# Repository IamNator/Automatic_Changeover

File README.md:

# Automatic Changeover
This project sets out to design a highly effective and efficient IOT enabled automatic changeover for small homes.    
With improvements and modifications as time goes by, this project will design devices capable of allowing the user to monitor their household energy comsumption.

## Files
**3d-module**: contains files of 3D design, (Fusion 360).   
**PCB**: PCB files, (EAGLE).   
**code-mcu**: C program files, (ATMEL Studio).   
**images**: Images of circuit, PCB and 3D designs.   

## How to access this project

 1. Navigate to the main page of this repository.
 2. Under the repository name (Automatic_Changeover), click Clone or download.
 3. In the Clone with HTTPs section, click on **Download Zip** to download this project as a zip file

## Sample Images

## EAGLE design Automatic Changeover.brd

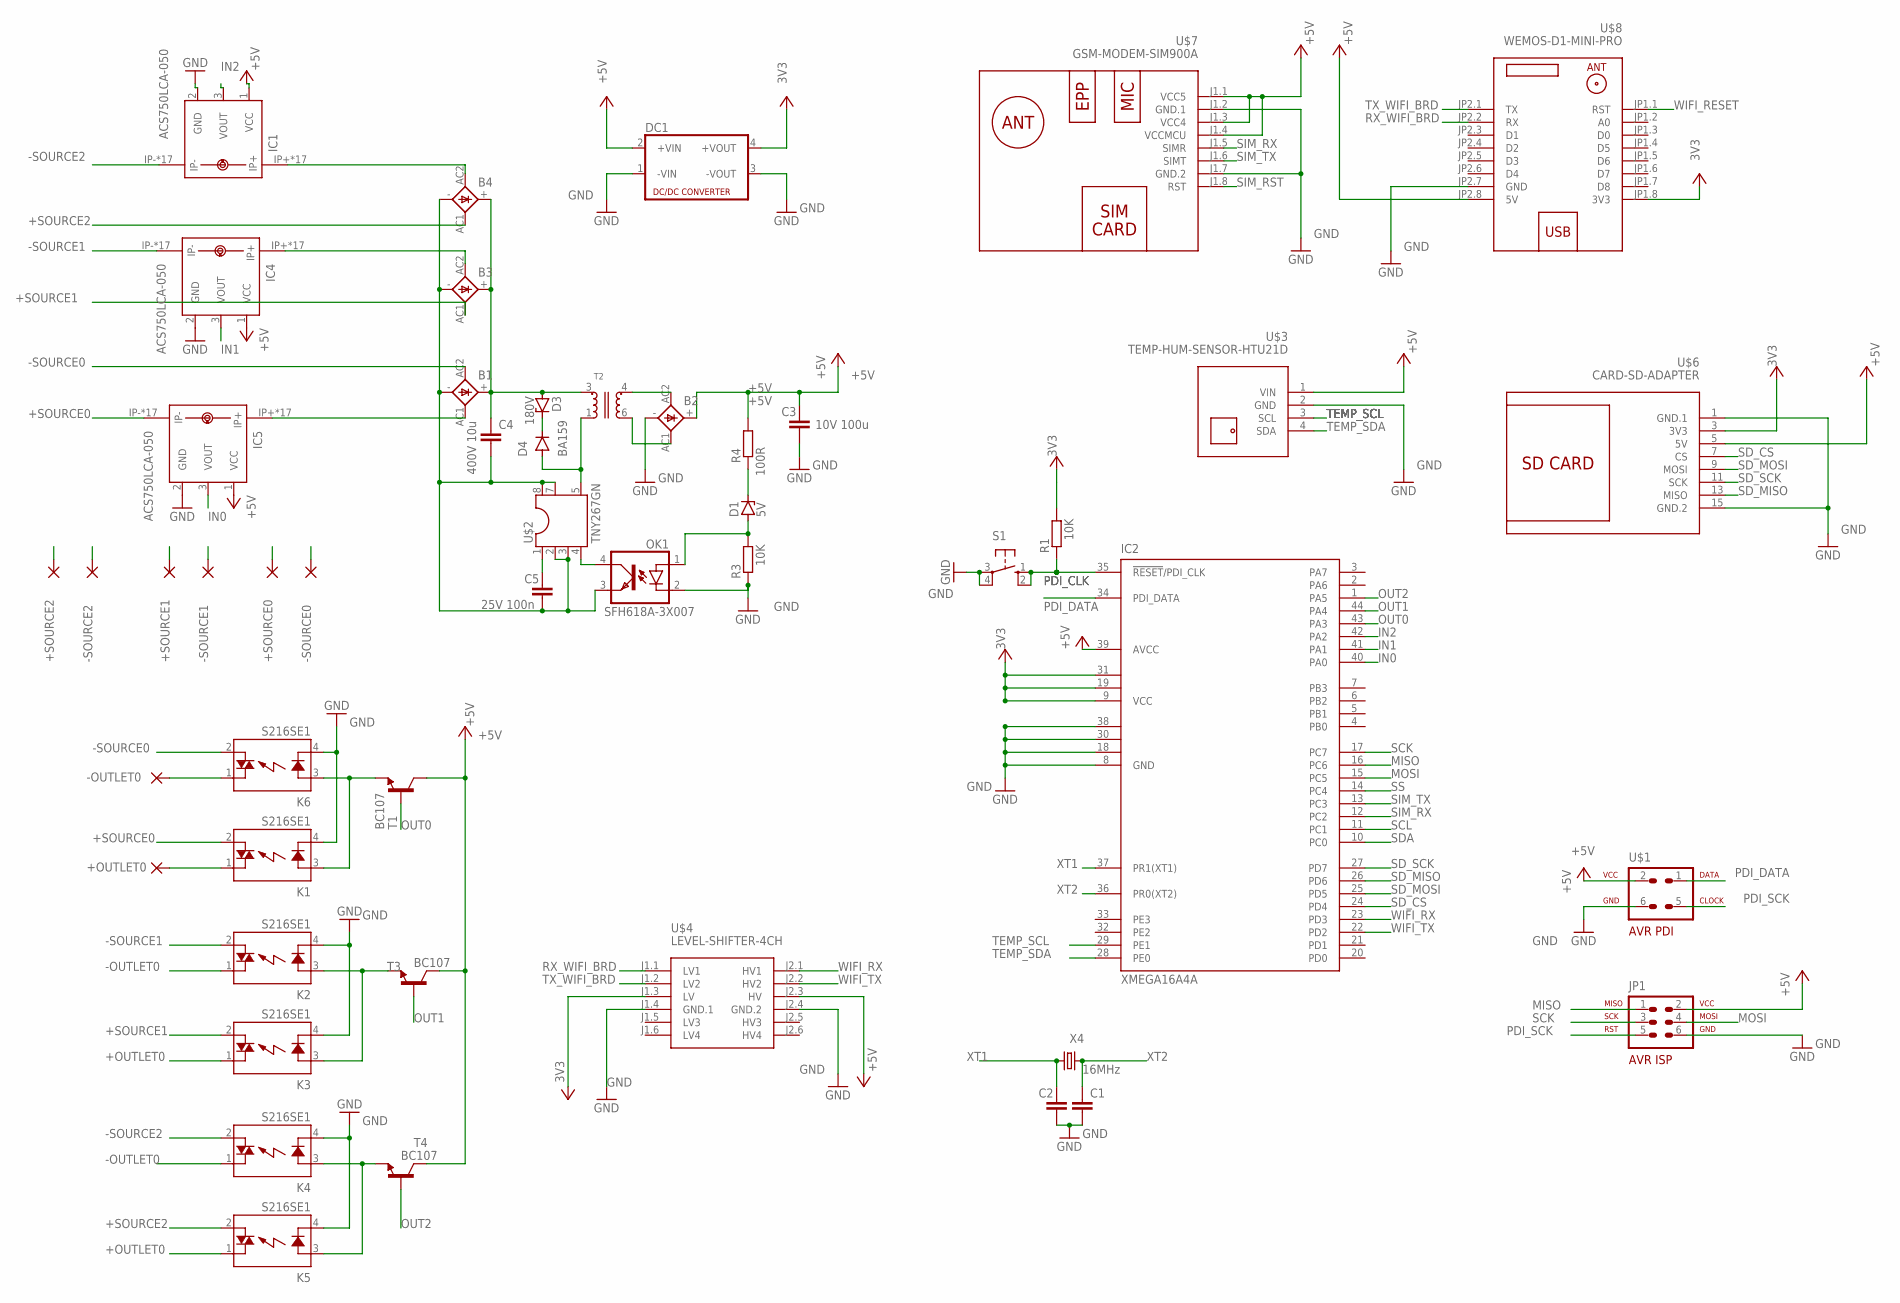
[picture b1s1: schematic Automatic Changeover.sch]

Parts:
+OUTLET0: 3,81/1,4
+SOURCE0, +SOURCE1, +SOURCE2: 3,81/1,4
-OUTLET0: 3,81/1,4
-SOURCE0, -SOURCE1, -SOURCE2: 3,81/1,4
B1, B2, B3, B4: KBL
C1, C2: C-EU025-025X050; C025-025X050
C3: 10V 100u; C2.5-2
C4: 400V 10u; C2.5-2
C5: 25V 100n; C2.5-2
D1: 5V; P1Z12
D3: 180V; P1Z12
D4: BA159; DO41-10
DC1: NME
IC1, IC4, IC5: ACS750LCA-050; ACS75050
IC2: XMEGA16A4A; TQFP44
JP1: AVR-ISP-6VERT; AVR-ISP-6
K1, K2, K3, K4, K5, K6: S216SE1; S2XXEX
OK1: SFH618A-3X007; SMD4-7
R1, R3: 10K; R0805
R4: 100R; R0805
S1: 10-XX; B3F-10XX
T1, T3, T4: BC107; TO18
T2: WE-UNIT_74911810X; WE_E13/7/4_THT_VERTIKAL_6PIN
U$1: AVR-PDIVERT; AVR-ISP-6
U$2: TNY267GN; SMD-8B
U$3: TEMP-HUM-SENSOR-HTU21D
U$4: LEVEL-SHIFTER-4CH
U$6: CARD-SD-ADAPTER
U$7: GSM-MODEM-SIM900A
U$8: WEMOS-D1-MINI-PRO
X4: 16MHz; HC49

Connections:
3V3: DC1.4 (+VOUT), R1.2, U$6.3 (3V3), U$8.JP1.8 (3V3)
+5V: B2.+, C3.1, DC1.2 (+VIN), IC1.1 (VCC), IC2.39 (AVCC), IC4.1 (VCC), IC5.1 (VCC), JP1.2, R4.2, T1.3 (C), T3.3 (C), T4.3 (C), U$1.2, U$3.1 (VIN), U$4.J2.3 (HV), U$6.5 (5V), U$7.J1.1 (VCC5), U$7.J1.3 (VCC4), U$7.J1.4 (VCCMCU), U$8.JP2.8 (5V)
+OUTLET0: K3.1 (DS1), K5.1 (DS1)
+SOURCE0: +SOURCE0.1, IC5.IP-, IC5.IP-@2 (IP-), IC5.IP-@3 (IP-), IC5.IP-@4 (IP-), IC5.IP-@5 (IP-), IC5.IP-@6 (IP-), IC5.IP-@7 (IP-), IC5.IP-@8 (IP-), IC5.IP-@9 (IP-), IC5.IP-@10 (IP-), IC5.IP-@11 (IP-), IC5.IP-@12 (IP-), IC5.IP-@13 (IP-), IC5.IP-@14 (IP-), IC5.IP-@15 (IP-), IC5.IP-@16 (IP-), IC5.IP-@17 (IP-), K1.2 (DS2)
+SOURCE1: +SOURCE1.1, B3.AC1 (AC2), K3.2 (DS2)
+SOURCE2: +SOURCE2.1, B4.AC1 (AC2), K5.2 (DS2)
-OUTLET0: K2.1 (DS1), K4.1 (DS1)
-SOURCE0: -SOURCE0.1, B1.AC2 (AC1), K6.2 (DS2)
-SOURCE1: -SOURCE1.1, IC4.IP-, IC4.IP-@2 (IP-), IC4.IP-@3 (IP-), IC4.IP-@4 (IP-), IC4.IP-@5 (IP-), IC4.IP-@6 (IP-), IC4.IP-@7 (IP-), IC4.IP-@8 (IP-), IC4.IP-@9 (IP-), IC4.IP-@10 (IP-), IC4.IP-@11 (IP-), IC4.IP-@12 (IP-), IC4.IP-@13 (IP-), IC4.IP-@14 (IP-), IC4.IP-@15 (IP-), IC4.IP-@16 (IP-), IC4.IP-@17 (IP-), K2.2 (DS2)
-SOURCE2: -SOURCE2.1, IC1.IP-, IC1.IP-@2 (IP-), IC1.IP-@3 (IP-), IC1.IP-@4 (IP-), IC1.IP-@5 (IP-), IC1.IP-@6 (IP-), IC1.IP-@7 (IP-), IC1.IP-@8 (IP-), IC1.IP-@9 (IP-), IC1.IP-@10 (IP-), IC1.IP-@11 (IP-), IC1.IP-@12 (IP-), IC1.IP-@13 (IP-), IC1.IP-@14 (IP-), IC1.IP-@15 (IP-), IC1.IP-@16 (IP-), IC1.IP-@17 (IP-), K4.2 (DS2)
GND: B2.-, C1.2, C2.2, C3.2, DC1.1 (-VIN), DC1.3 (-VOUT), IC1.2 (GND), IC2.8 (GND), IC2.18 (GND1), IC2.30 (GND2), IC2.38 (GND3), IC4.2 (GND), IC5.2 (GND), JP1.6, K1.4 (K), K2.4 (K), K3.4 (K), K4.4 (K), K5.4 (K), K6.4 (K), OK1.2 (C), R3.1, S1.3, S1.4 (P1), U$1.6, U$3.2 (GND), U$4.J1.4 (GND.1), U$4.J2.4 (GND.2), U$6.1 (GND.1), U$6.15 (GND.2), U$7.J1.2 (GND.1), U$7.J1.7 (GND.2), U$8.JP2.7 (GND)
IN0: IC2.40 (PA0), IC5.3 (VOUT)
IN1: IC2.41 (PA1), IC4.3 (VOUT)
IN2: IC1.3 (VOUT), IC2.42 (PA2)
MISO: IC2.16 (PC6), JP1.1
MOSI: IC2.15 (PC5), JP1.4
unnamed: B4.AC2 (AC1), IC1.IP+, IC1.IP+@2 (IP+), IC1.IP+@3 (IP+), IC1.IP+@4 (IP+), IC1.IP+@5 (IP+), IC1.IP+@6 (IP+), IC1.IP+@7 (IP+), IC1.IP+@8 (IP+), IC1.IP+@9 (IP+), IC1.IP+@10 (IP+), IC1.IP+@11 (IP+), IC1.IP+@12 (IP+), IC1.IP+@13 (IP+), IC1.IP+@14 (IP+), IC1.IP+@15 (IP+), IC1.IP+@16 (IP+), IC1.IP+@17 (IP+)
unnamed: B1.AC1 (AC2), IC5.IP+, IC5.IP+@2 (IP+), IC5.IP+@3 (IP+), IC5.IP+@4 (IP+), IC5.IP+@5 (IP+), IC5.IP+@6 (IP+), IC5.IP+@7 (IP+), IC5.IP+@8 (IP+), IC5.IP+@9 (IP+), IC5.IP+@10 (IP+), IC5.IP+@11 (IP+), IC5.IP+@12 (IP+), IC5.IP+@13 (IP+), IC5.IP+@14 (IP+), IC5.IP+@15 (IP+), IC5.IP+@16 (IP+), IC5.IP+@17 (IP+)
unnamed: B1.+, B3.+, B4.+, C4.1, D3.A, T2.3 (1)
unnamed: B3.AC2 (AC1), IC4.IP+, IC4.IP+@2 (IP+), IC4.IP+@3 (IP+), IC4.IP+@4 (IP+), IC4.IP+@5 (IP+), IC4.IP+@6 (IP+), IC4.IP+@7 (IP+), IC4.IP+@8 (IP+), IC4.IP+@9 (IP+), IC4.IP+@10 (IP+), IC4.IP+@11 (IP+), IC4.IP+@12 (IP+), IC4.IP+@13 (IP+), IC4.IP+@14 (IP+), IC4.IP+@15 (IP+), IC4.IP+@16 (IP+), IC4.IP+@17 (IP+)
unnamed: -OUTLET0.1, K6.1 (DS1)
unnamed: D4.A, T2.1 (4), U$2.5 (D)
unnamed: B2.AC1 (AC2), T2.6 (3)
unnamed: D1.C, R4.1
unnamed: D1.A, OK1.1 (A), R3.2
unnamed: B1.-, B3.-, B4.-, C4.2, C5.2, OK1.3 (EMIT), U$2.2 (2GND), U$2.3 (3GND), U$2.7 (7HV-GND), U$2.8 (8HV-GND)
unnamed: B2.AC2 (AC1), T2.4 (2)
unnamed: D3.C, D4.C
unnamed: C5.1, U$2.1 (BP)
unnamed: OK1.4 (COL), U$2.4 (EN/UV)
unnamed: +OUTLET0.1, K1.1 (DS1)
unnamed: K1.3 (A), K6.3 (A), T1.1 (E)
unnamed: K2.3 (A), K3.3 (A), T3.1 (E)
unnamed: K4.3 (A), K5.3 (A), T4.1 (E)
OUT0: IC2.43 (PA3), T1.2 (B)
OUT1: IC2.44 (PA4), T3.2 (B)
OUT2: IC2.1 (PA5), T4.2 (B)
PDI_CLK: IC2.35 (!RESET!/PDI_CLK), R1.1, S1.1 (S), S1.2 (S1)
PDI_DATA: IC2.34 (PDI_DATA), U$1.1
PDI_SCK: JP1.5, U$1.5
RX_WIFI_BRD: U$4.J1.1 (LV1), U$8.JP2.2 (RX)
SCK: IC2.17 (PC7), JP1.3
SCL: IC2.11 (PC1)
SDA: IC2.10 (PC0)
SD_CS: IC2.24 (PD4), U$6.7 (CS)
SD_MISO: IC2.26 (PD6), U$6.13 (MISO)
SD_MOSI: IC2.25 (PD5), U$6.9 (MOSI)
SD_SCK: IC2.27 (PD7), U$6.11 (SCK)
SIM_RST: U$7.J1.8 (RST)
SIM_RX: IC2.12 (PC2), U$7.J1.5 (SIMR)
SIM_TX: IC2.13 (PC3), U$7.J1.6 (SIMT)
SS: IC2.14 (PC4)
TEMP_SCL: IC2.29 (PE1), U$3.3 (SCL)
TEMP_SDA: IC2.28 (PE0), U$3.4 (SDA)
TX_WIFI_BRD: U$4.J1.2 (LV2), U$8.JP2.1 (TX)
VCC: IC2.9 (VCC), IC2.19 (VCC1), IC2.31 (VCC2), U$4.J1.3 (LV)
WIFI_RESET: U$8.JP1.1 (RST)
WIFI_RX: IC2.23 (PD3), U$4.J2.1 (HV1)
WIFI_TX: IC2.22 (PD2), U$4.J2.2 (HV2)
XT1: C2.1, IC2.37 (PR1(XT1)), X4.1
XT2: C1.1, IC2.36 (PR0(XT2)), X4.2

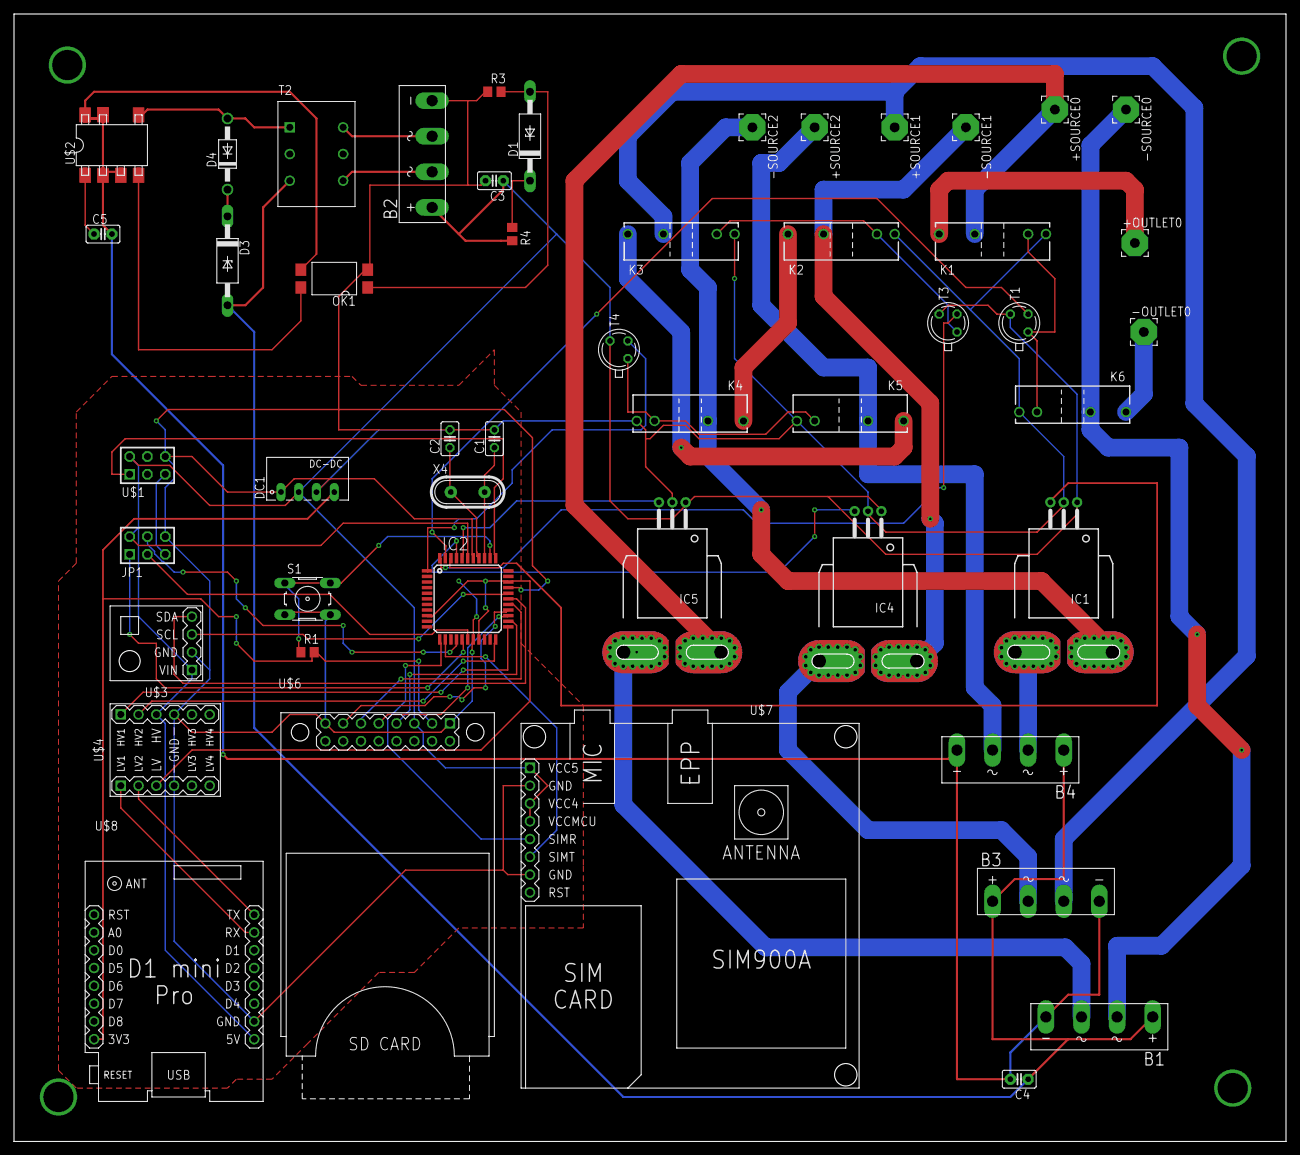
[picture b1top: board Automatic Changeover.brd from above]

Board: 2 copper layers, 181.6 x 161.0 mm, 49 parts (0 on the bottom side), 56 nets.

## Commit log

2020-07-03 3V3 and 5V changes
2020-07-03 You won't believe the amount of embrassing flaws that were corrected
2020-07-03 In the middle of changing the polarity of the SSR relays and also added SD_CS to MCU
2020-07-03 completed polarity reversion of SSR relays
2020-07-03 Adding a package.json to store important information about this project
2020-07-03 minor change on main MCU
2020-07-16 Just about to build board
2020-07-16 experimenting
2020-07-16 deleted experimental files
2020-07-16 just add *.brd file -- PCB created
2020-07-16 corrected an error in schematic
2020-07-16 add pad through hole for power source connection
2020-07-16 placed all components on board
2020-07-16 first Auto-route
2020-07-16 rearranged the crystal and capactitor for it
2020-07-16 adjusted many components to desired position
2020-07-16 good arrangement
2020-07-16 added 100mil trace to connect AC wires
2020-07-16 Finished manually routing AC wires
2020-07-16 correcting route errors
2020-07-16 almost done--just trace with of high DC current left
2020-07-16 about to finish
2020-07-16 done resizing
2020-07-16 a few important refinement
2020-07-16 added a gerber file of it
2020-07-16 added ground plane
2020-07-16 Some few adjustments
2020-07-16 Just saving Works
2020-07-16 Perfecting the traces
2020-07-17 Fine tunning the board
2020-07-18 reorganised my files
2020-07-18 Rearranged the files
2020-07-18 added a README.md file
2020-07-18 modified README.md file
2020-07-18 Putting Schmatic and PCB files in one folder
2020-07-18 initialized Atmel project file in code-mcu
2020-07-18 adding a 3d-module folder
2020-07-18 modified package.json file
2020-07-18 Added ASF (Advanced Software Framework) Driver Modules to Atmel project
2020-07-21 Added hem hem and aiyede to project authors in package.json file
2020-07-21 Updating README.md file
2020-07-21 Adding pictures to README.md file
2020-07-22 Updated code-mcu files --- configuring USART
2020-07-23 updating README.md
2020-07-23 changing image size
2020-07-23 spelling corrections
2020-07-23 spelling correction
2020-07-23 Adjusting image sizes
2020-07-23 Minor changes
2020-07-23 adding ko fi
2020-07-25 small changes

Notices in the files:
parts and their libraries:
Wurth_Elektronik_Passive_rev16b: Copyright: Würth Elektronik
diy-modules: Released under the Creative Commons Attribution 4.0 International License: http://creativecommons.org/licenses/by/4.0
